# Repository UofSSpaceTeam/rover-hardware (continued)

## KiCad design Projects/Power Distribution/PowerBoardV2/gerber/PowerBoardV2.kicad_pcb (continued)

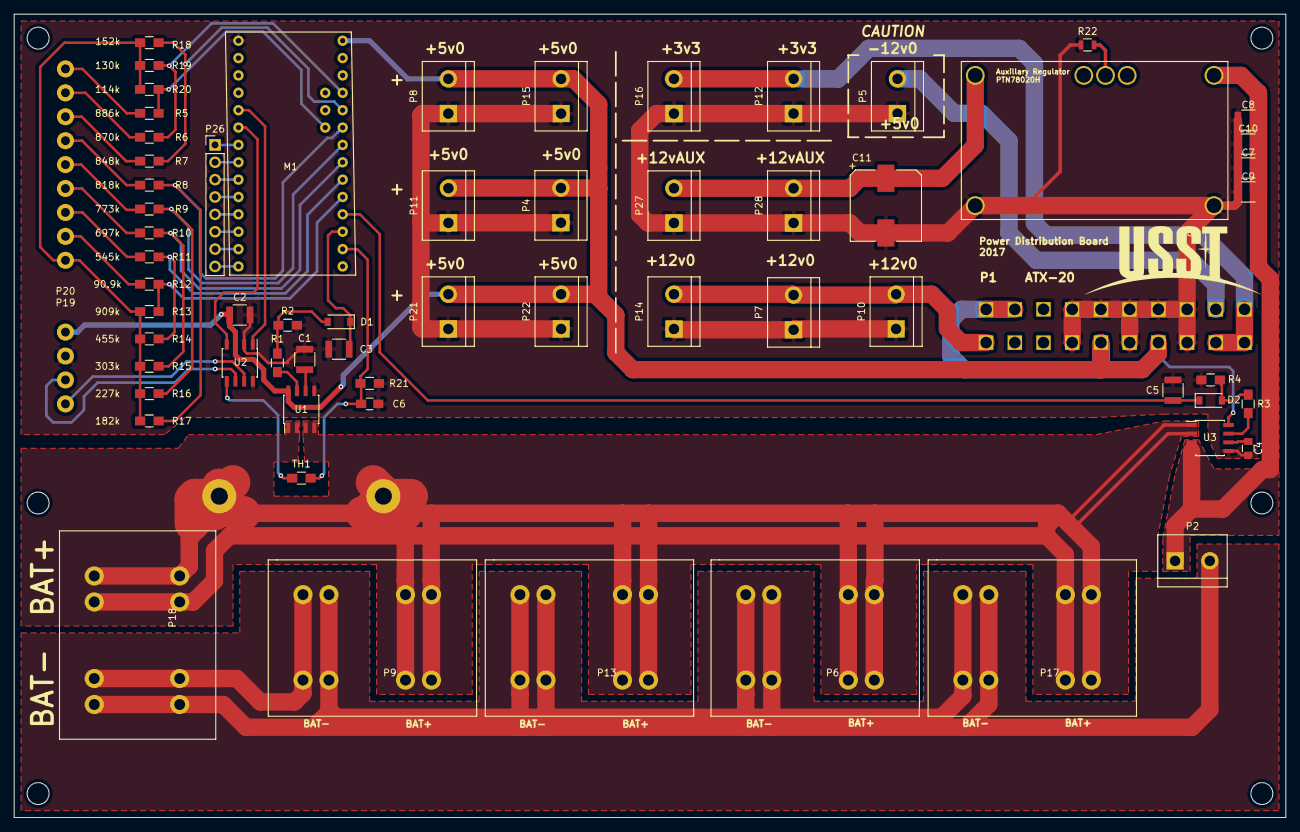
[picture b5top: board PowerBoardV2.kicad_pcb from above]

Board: 2 copper layers, 186.0 x 117.5 mm, 65 parts (1 on the bottom side), 49 nets.

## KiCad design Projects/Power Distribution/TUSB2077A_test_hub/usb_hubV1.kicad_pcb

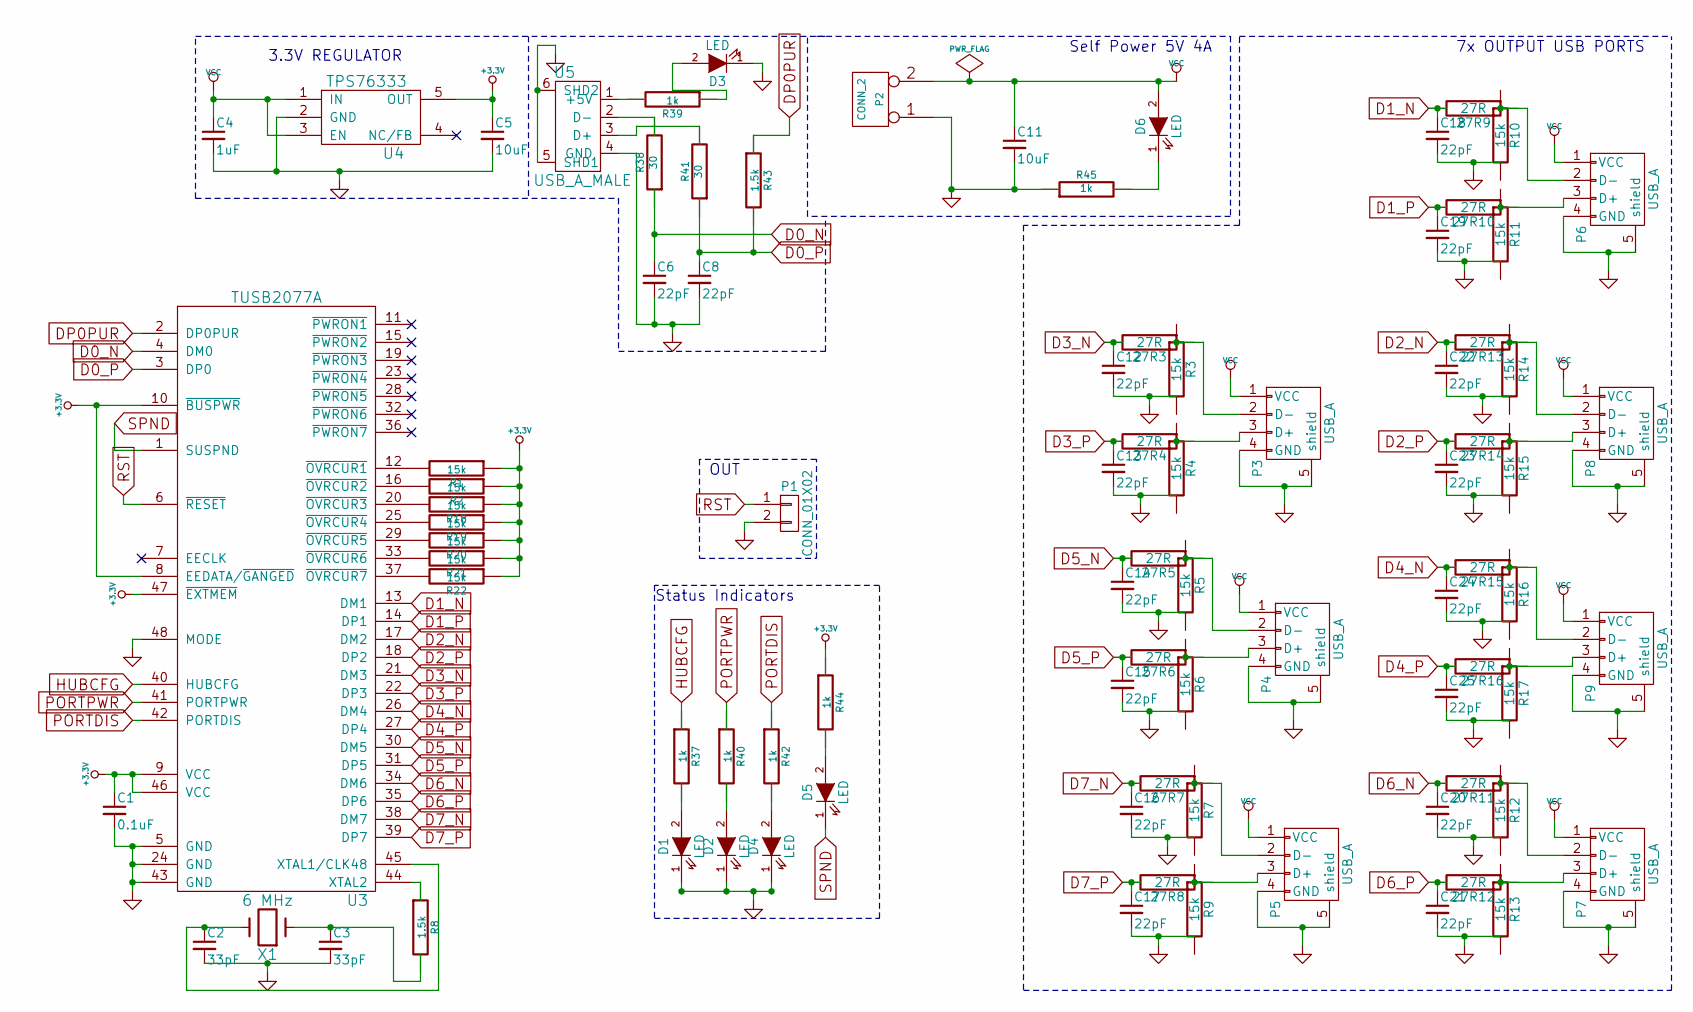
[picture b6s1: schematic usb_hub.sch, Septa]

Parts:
27R3, 27R4, 27R5, 27R6, 27R7, 27R8, 27R9, 27R10, 27R11, 27R12, 27R13, 27R14, 27R15: 27R; R_0805
27R16: 27R; C_0805
C1: 0.1uF; C_0805
C2, C3: 33pF; C_0805
C4: 1uF; C_0805
C5, C11: 10uF; C_0805
C6, C8, C12, C13, C14, C15, C16, C17, C18, C19, C20, C21, C22, C23, C24, C25: 22pF; C_0805
D1, D2, D3, D4, D5, D6: LED; LED_0805; MFRPN APT1608SGC; DIGIKEY 754-1121-6-ND
P1: CONN_01X02; Pin_Header_Straight_1x02
P2: CONN_2; Pin_Header_Straight_1x02
P3, P4, P5, P6, P7, P8, P9: USB_A
R1, R2, R3, R4, R5, R6, R7, R9, R10, R11, R12, R13, R14, R15, R16, R17, R18, R19, R20, R21, R22: 15k; R_0805
R8, R43: 1.5k; R_0805; MFRPN ESR03EZPJ152; DIGIKEY RHM1.5KDDKR-ND
R37, R39, R40, R42, R44, R45: 1k; R_0805; MFRPN ESR03EZPJ102; DIGIKEY RHM1.0KDDKR-ND
R38, R41: 30; R_0805; MFRPN ERJ3EKF30R0V; DIGIKEY RHM30DDKR-ND
U3: TUSB2077A; TQFP-48_7x7mm_Pitch0.5mm; MFRPN TUSB2077APTR; DIGIKEY 296-37871-6-ND
U4: TPS76333; SOT-23-5; MFRPN TPS76333DBVR; DIGIKEY 296-11021-6-ND
U5: USB_A_MALE; USB_Mini-B; MFRPN 0473461001; DIGIKEY Value
X1: 6 MHz; FOX6MHZ; MFRPN FQ1045A6000; DIGIKEY 631-1035-6-ND

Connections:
+3.3V: C1.1, C5.1, R1.1, R2.1, R18.1, R19.1, R20.1, R21.1, R22.1, R44.1, U3.8 (EEDATA/~GANGED), U3.9 (VCC), U3.10 (~BUSPWR), U3.46 (VCC), U3.47 (~EXTMEM), U4.5 (OUT)
D0_N: C6.1, R38.1, U3.4 (DM0)
D0_P: C8.1, R41.1, R43.2, U3.3 (DP0)
D1_N: 27R9.2, C18.1, U3.13 (DM1)
D1_P: 27R10.2, C19.1, U3.14 (DP1)
D2_N: 27R13.2, C22.1, U3.17 (DM2)
D2_P: 27R14.2, C23.1, U3.18 (DP2)
D3_N: 27R3.2, C12.1, U3.21 (DM3)
D3_P: 27R4.2, C13.1, U3.22 (DP3)
D4_N: 27R15.2, C24.1, U3.26 (DM4)
D4_P: 27R16.2, C25.1, U3.27 (DP4)
D5_N: 27R5.2, C14.1, U3.30 (DM5)
D5_P: 27R6.2, C15.1, U3.31 (DP5)
D6_N: 27R11.2, C20.1, U3.34 (DM6)
D6_P: 27R12.2, C21.1, U3.35 (DP6)
D7_N: 27R7.2, C16.1, U3.38 (DM7)
D7_P: 27R8.2, C17.1, U3.39 (DP7)
DP0PUR: R43.1, U3.2 (DP0PUR)
GND: C1.2, C2.2, C3.2, C4.2, C5.2, C6.2, C8.2, C11.2, C12.2, C13.2, C14.2, C15.2, C16.2, C17.2, C18.2, C19.2, C20.2, C21.2, C22.2, C23.2, C24.2, C25.2, D1.1 (K), D2.1 (K), D3.1 (K), D4.1 (K), P1.2, P2.1, P3.4 (GND), P3.5 (shield), P4.4 (GND), P4.5 (shield), P5.4 (GND), P5.5 (shield), P6.4 (GND), P6.5 (shield), P7.4 (GND), P7.5 (shield), P8.4 (GND), P8.5 (shield), P9.4 (GND), P9.5 (shield), R3.2, R4.2, R5.2, R6.2, R7.2, R9.2, R10.2, R11.2, R12.2, R13.2, R14.2, R15.2, R16.2, R17.2, R45.1, U3.5 (GND), U3.24 (GND), U3.43 (GND), U3.48 (MODE), U4.2 (GND), U5.4 (GND), U5.5 (SHD1), U5.6 (SHD2)
HUBCFG: R37.1, U3.40 (HUBCFG)
unnamed: 27R3.1, P3.2 (D-), R3.1
unnamed: 27R4.1, P3.3 (D+), R4.1
unnamed: 27R5.1, P4.2 (D-), R5.1
unnamed: 27R6.1, P4.3 (D+), R6.1
unnamed: 27R7.1, P5.2 (D-), R7.1
unnamed: 27R8.1, P5.3 (D+), R9.1
unnamed: 27R9.1, P6.2 (D-), R10.1
unnamed: 27R10.1, P6.3 (D+), R11.1
unnamed: 27R11.1, P7.2 (D-), R12.1
unnamed: 27R12.1, P7.3 (D+), R13.1
unnamed: 27R13.1, P8.2 (D-), R14.1
unnamed: 27R14.1, P8.3 (D+), R15.1
unnamed: 27R15.1, P9.2 (D-), R16.1
unnamed: 27R16.1, P9.3 (D+), R17.1
unnamed: C2.1, U3.45 (XTAL1/CLK48), X1.2
unnamed: D1.2 (A), R37.2
unnamed: D2.2 (A), R40.2
unnamed: D3.2 (A), R39.1
unnamed: D4.2 (A), R42.2
unnamed: D5.2 (A), R44.2
unnamed: D6.1 (K), R45.2
unnamed: R1.2, U3.12 (~OVRCUR1)
unnamed: R2.2, U3.16 (~OVRCUR2)
unnamed: R8.1, U3.44 (XTAL2)
unnamed: R18.2, U3.20 (~OVRCUR3)
unnamed: R19.2, U3.25 (~OVRCUR4)
unnamed: R20.2, U3.29 (~OVRCUR5)
unnamed: R21.2, U3.33 (~OVRCUR6)
unnamed: R22.2, U3.37 (~OVRCUR7)
unnamed: R38.2, U5.2 (D-)
unnamed: R39.2, U5.1 (+5V)
unnamed: R41.2, U5.3 (D+)
PORTDIS: R42.1, U3.42 (PORTDIS)
PORTPWR: R40.1, U3.41 (PORTPWR)
RST: P1.1, U3.6 (~RESET)
SPND: D5.1 (K), U3.1 (SUSPND)
VCC: C4.1, C11.1, D6.2 (A), P2.2 (PM), P3.1 (VCC), P4.1 (VCC), P5.1 (VCC), P6.1 (VCC), P7.1 (VCC), P8.1 (VCC), P9.1 (VCC), U4.1 (IN), U4.3 (EN)

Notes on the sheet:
Self Power 5V 4A
7x OUTPUT USB PORTS
3.3V REGULATOR
Status Indicators
OUT

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
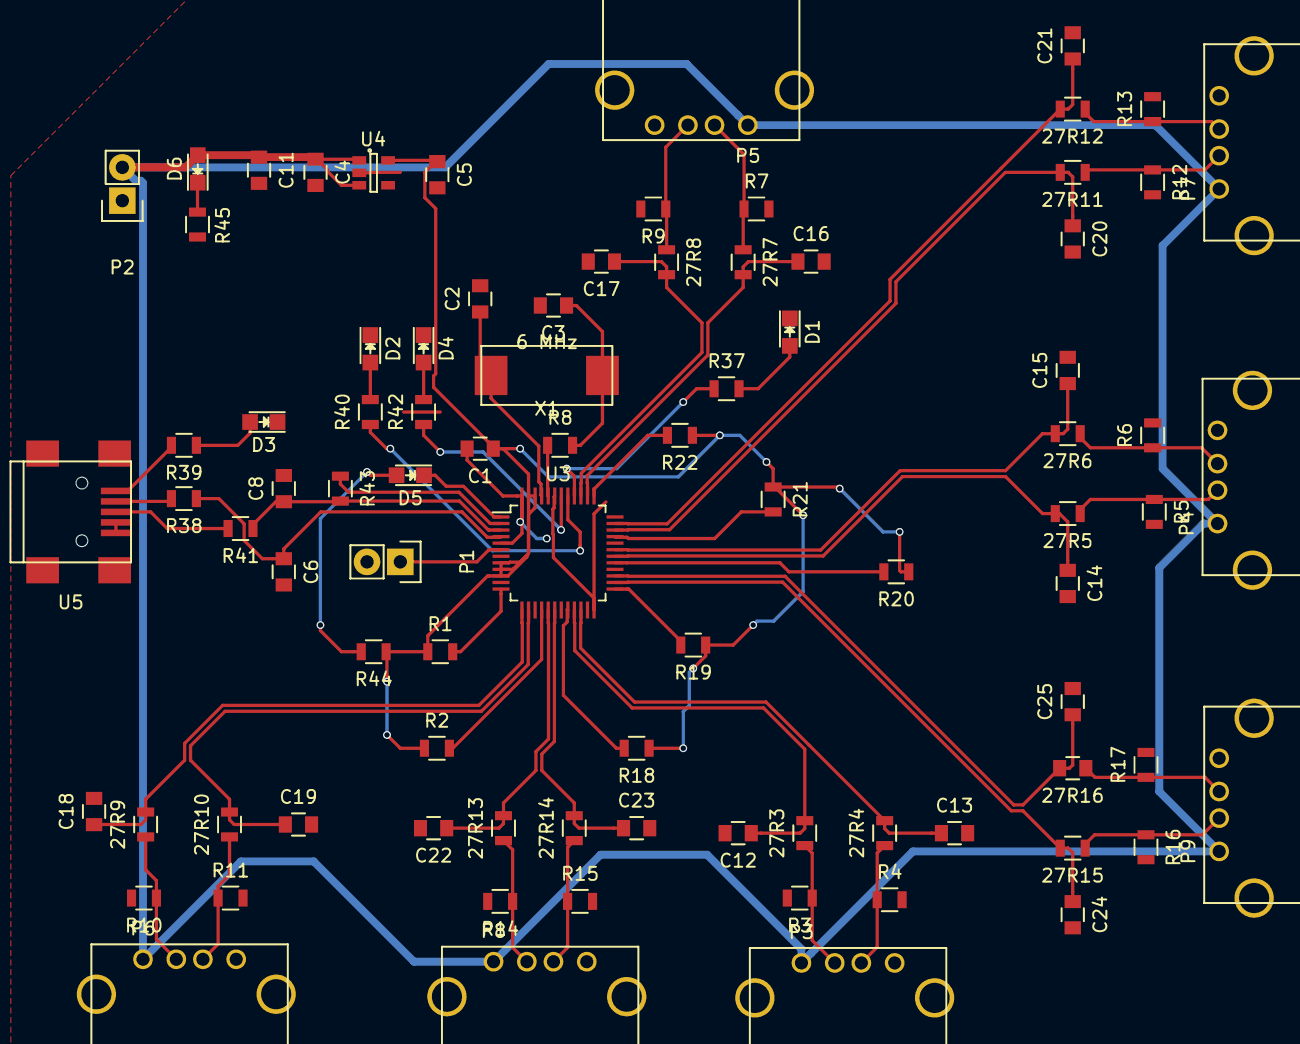
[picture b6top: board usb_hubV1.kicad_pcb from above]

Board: 2 copper layers, 86 parts (0 on the bottom side), 58 nets.
